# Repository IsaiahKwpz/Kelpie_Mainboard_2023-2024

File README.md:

# Kelpie_Mainboard(2023-2024)
 This is the Mainboard I designed for the kelpie robotics 2023-2024 season. It contains many sensors required to complete various tasks at the competition. It also houses an orange Pi, and a pi pico for communication across components. It is powered by a motherboard like PCB, which the mainboard is designed to slot into.

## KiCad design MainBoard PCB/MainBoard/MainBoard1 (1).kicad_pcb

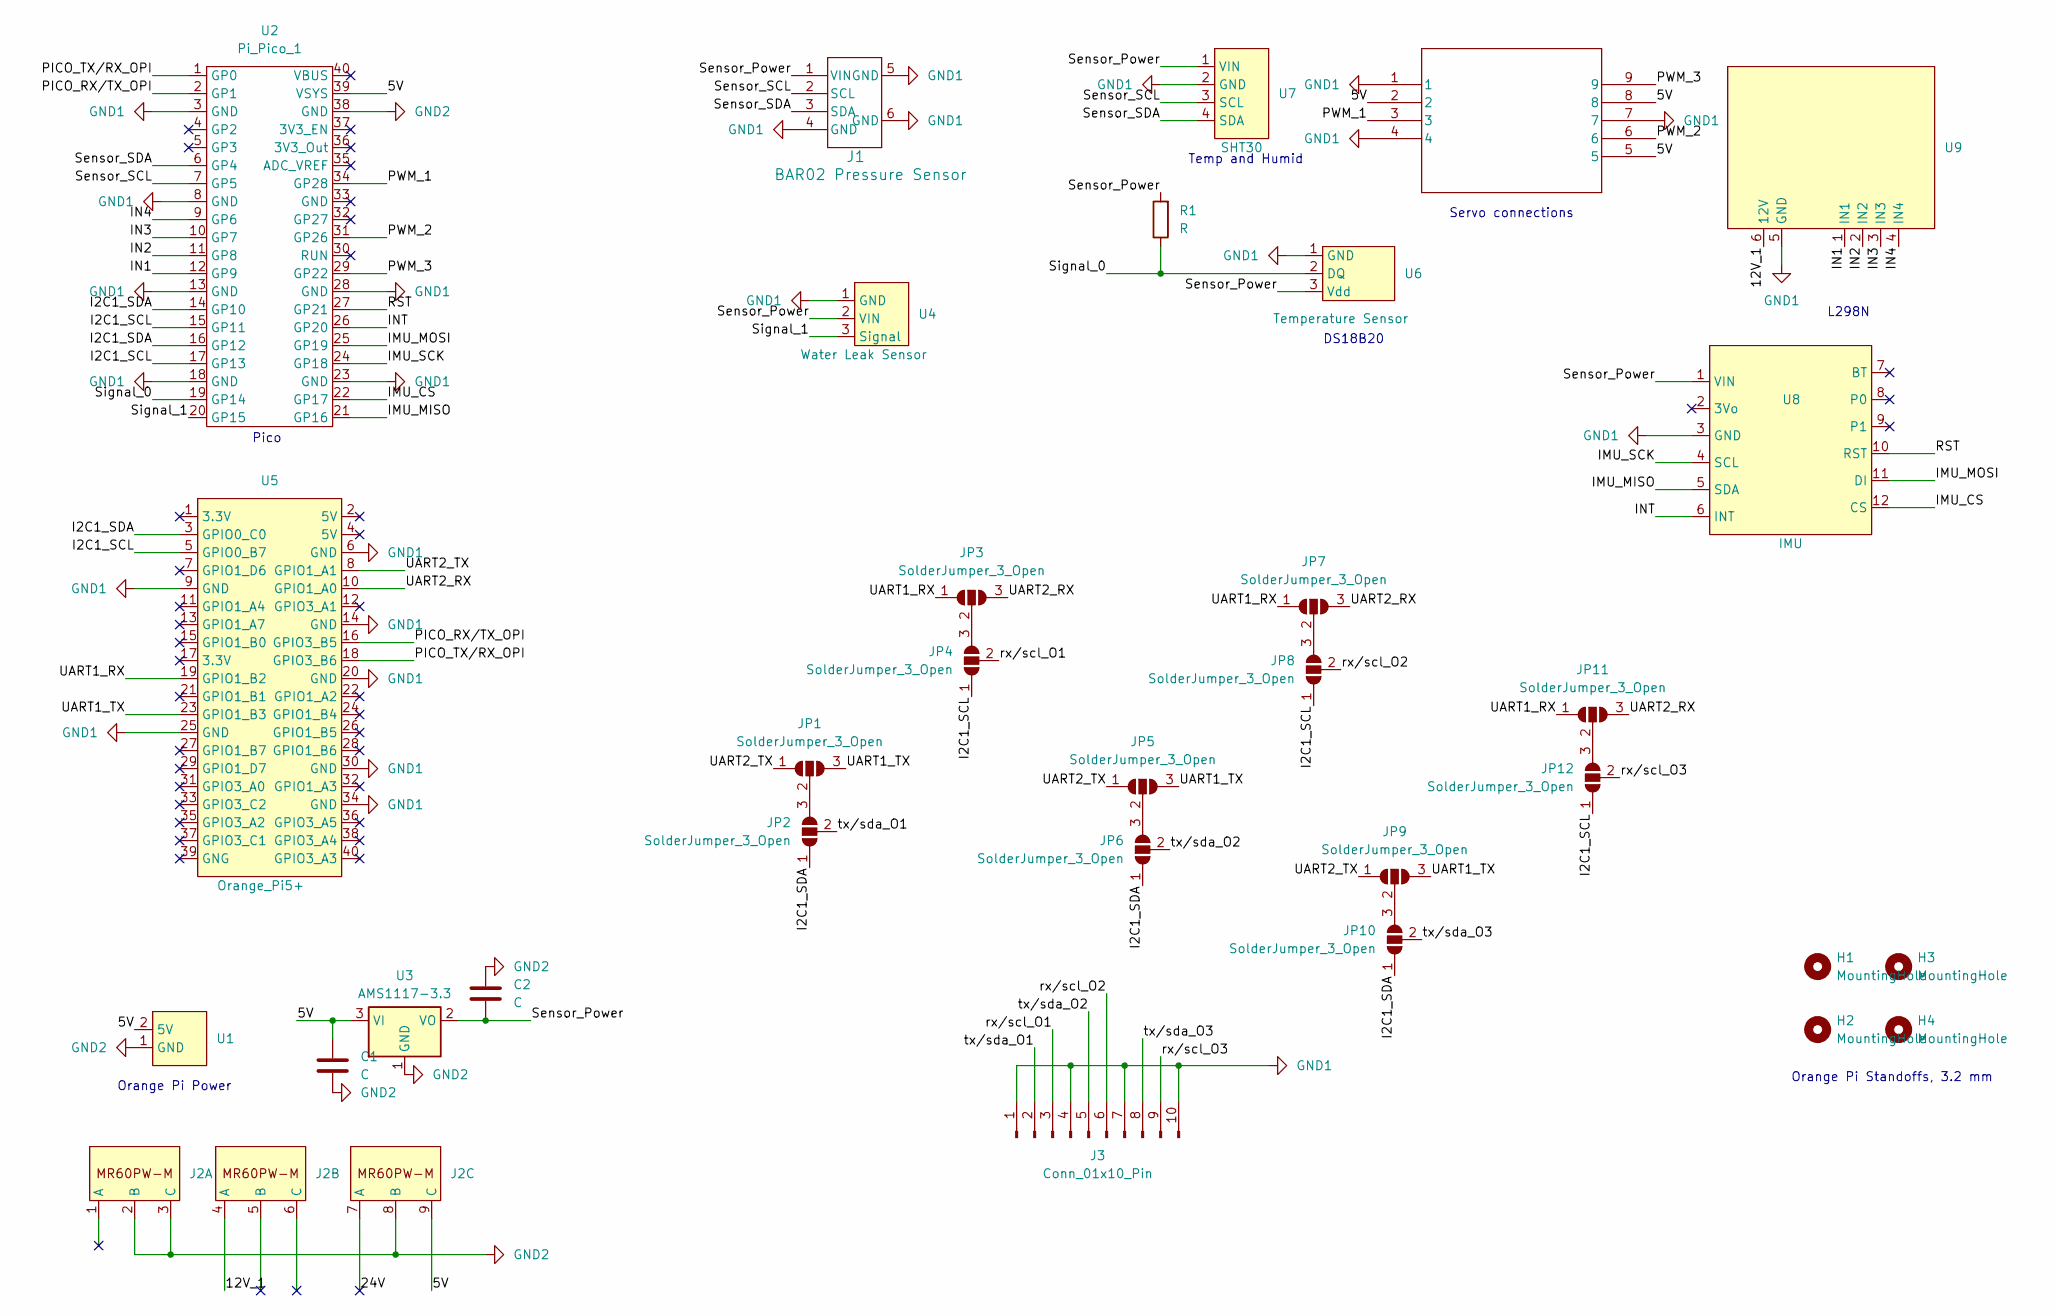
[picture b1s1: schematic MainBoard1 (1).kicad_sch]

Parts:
C1, C2: C; C_0805_2012Metric_Pad1.18x1.45mm_HandSolder
H1, H2, H3, H4: MountingHole; MountingHole_3.2mm_M3
J1: BAR02 Pressure Sensor; JST
J2: MR60PW-M_X3 (2)
J3: Conn_01x10_Pin; CardEdge_2x10 (2)
J4: TSW-103-08-G-T-RA; TSW-103-08-T-T-RA_SAI
JP1, JP2, JP3, JP4, JP5, JP6, JP7, JP8, JP9, JP10, JP11, JP12: SolderJumper_3_Open; SolderJumper-3_P2.0mm_Open_TrianglePad1.0x1.5mm
R1: R; R_0805_2012Metric_Pad1.20x1.40mm_HandSolder
U1: PinHeader_1x02_P2.54mm_Horizontal
U2: Pi_Pico_1; ESP32-S3-Pico
U3: AMS1117-3.3; SOT-223-3_TabPin2
U4: Water Leak Sensor; PinHeader_1x03_P2.54mm_Horizontal
U5: Orange_Pi5+; PinHeader_2x20_P2.54mm_Vertical
U6: Temperature Sensor; PinHeader_1x03_P2.54mm_Horizontal
U7: SHT30
U8: IMU
U9: L298N

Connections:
/5V: C1.2, J2.9 (C), J4.2, J4.5, J4.8, U1.2 (5V), U2.39 (VSYS), U3.3 (VI)
/12V_1: J2.4 (A), U9.6 (12V)
/24V: J2.7 (A)
/I2C1_SCL: JP4.1 (A), JP8.1 (A), JP12.1 (A), U2.15 (GP11), U2.17 (GP13), U5.5 (GPIO0_B7)
/I2C1_SDA: JP2.1 (A), JP6.1 (A), JP10.1 (A), U2.14 (GP10), U2.16 (GP12), U5.3 (GPIO0_C0)
/IMU_CS: U2.22 (GP17), U8.12 (CS)
/IMU_MISO: U2.21 (GP16), U8.5 (SDA)
/IMU_MOSI: U2.25 (GP19), U8.11 (DI)
/IMU_SCK: U2.24 (GP18), U8.4 (SCL)
/IN1: U2.12 (GP9), U9.1 (IN1)
/IN2: U2.11 (GP8), U9.2 (IN2)
/IN3: U2.10 (GP7), U9.3 (IN3)
/IN4: U2.9 (GP6), U9.4 (IN4)
/INT: U2.26 (GP20), U8.6 (INT)
/PICO_RX/TX_OPI: U2.2 (GP1), U5.16 (GPIO3_B5)
/PICO_TX/RX_OPI: U2.1 (GP0), U5.18 (GPIO3_B6)
/PWM_1: J4.3, U2.34 (GP28)
/PWM_2: J4.6, U2.31 (GP26)
/PWM_3: J4.9, U2.29 (GP22)
/RST: U2.27 (GP21), U8.10 (RST)
/Sensor_Power: C2.1, J1.1 (VIN), R1.2, U3.2 (VO), U4.2 (VIN), U6.3 (Vdd), U7.1 (VIN), U8.1 (VIN)
/Sensor_SCL: J1.2 (SCL), U2.7 (GP5), U7.3 (SCL)
/Sensor_SDA: J1.3 (SDA), U2.6 (GP4), U7.4 (SDA)
/Signal_0: R1.1, U2.19 (GP14), U6.2 (DQ)
/Signal_1: U2.20 (GP15), U4.3 (Signal)
/UART1_RX: JP3.1 (A), JP7.1 (A), JP11.1 (A), U5.19 (GPIO1_B2)
/UART1_TX: JP1.3 (B), JP5.3 (B), JP9.3 (B), U5.23 (GPIO1_B3)
/UART2_RX: JP3.3 (B), JP7.3 (B), JP11.3 (B), U5.10 (GPIO1_A0)
/UART2_TX: JP1.1 (A), JP5.1 (A), JP9.1 (A), U5.8 (GPIO1_A1)
/rx/scl_O1: J3.3, JP4.2 (C)
/rx/scl_O2: J3.6, JP8.2 (C)
/rx/scl_O3: J3.9, JP12.2 (C)
/tx/sda_O1: J3.2, JP2.2 (C)
/tx/sda_O2: J3.5, JP6.2 (C)
/tx/sda_O3: J3.8, JP10.2 (C)
GND1: J1.4 (GND), J1.5 (GND), J1.6 (GND), J3.1, J3.4, J3.7, J3.10, J4.1, J4.4, J4.7, U2.3 (GND), U2.8 (GND), U2.13 (GND), U2.18 (GND), U2.23 (GND), U2.28 (GND), U4.1 (GND), U5.6 (GND), U5.9 (GND), U5.14 (GND), U5.20 (GND), U5.25 (GND), U5.30 (GND), U5.34 (GND), U6.1 (GND), U7.2 (GND), U8.3 (GND), U9.5 (GND)
GND2: C1.1, C2.2, J2.2 (B), J2.3 (C), J2.8 (B), U1.1 (GND), U2.38 (GND), U3.1 (GND)
unnamed: JP1.2 (C), JP2.3 (B)
unnamed: JP3.2 (C), JP4.3 (B)
unnamed: JP5.2 (C), JP6.3 (B)
unnamed: JP7.2 (C), JP8.3 (B)
unnamed: JP9.2 (C), JP10.3 (B)
unnamed: JP11.2 (C), JP12.3 (B)

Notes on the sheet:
DS18B20
Orange Pi Power
Orange Pi Standoffs, 3.2 mm
Servo connections
Temp and Humid
L298N
Pico

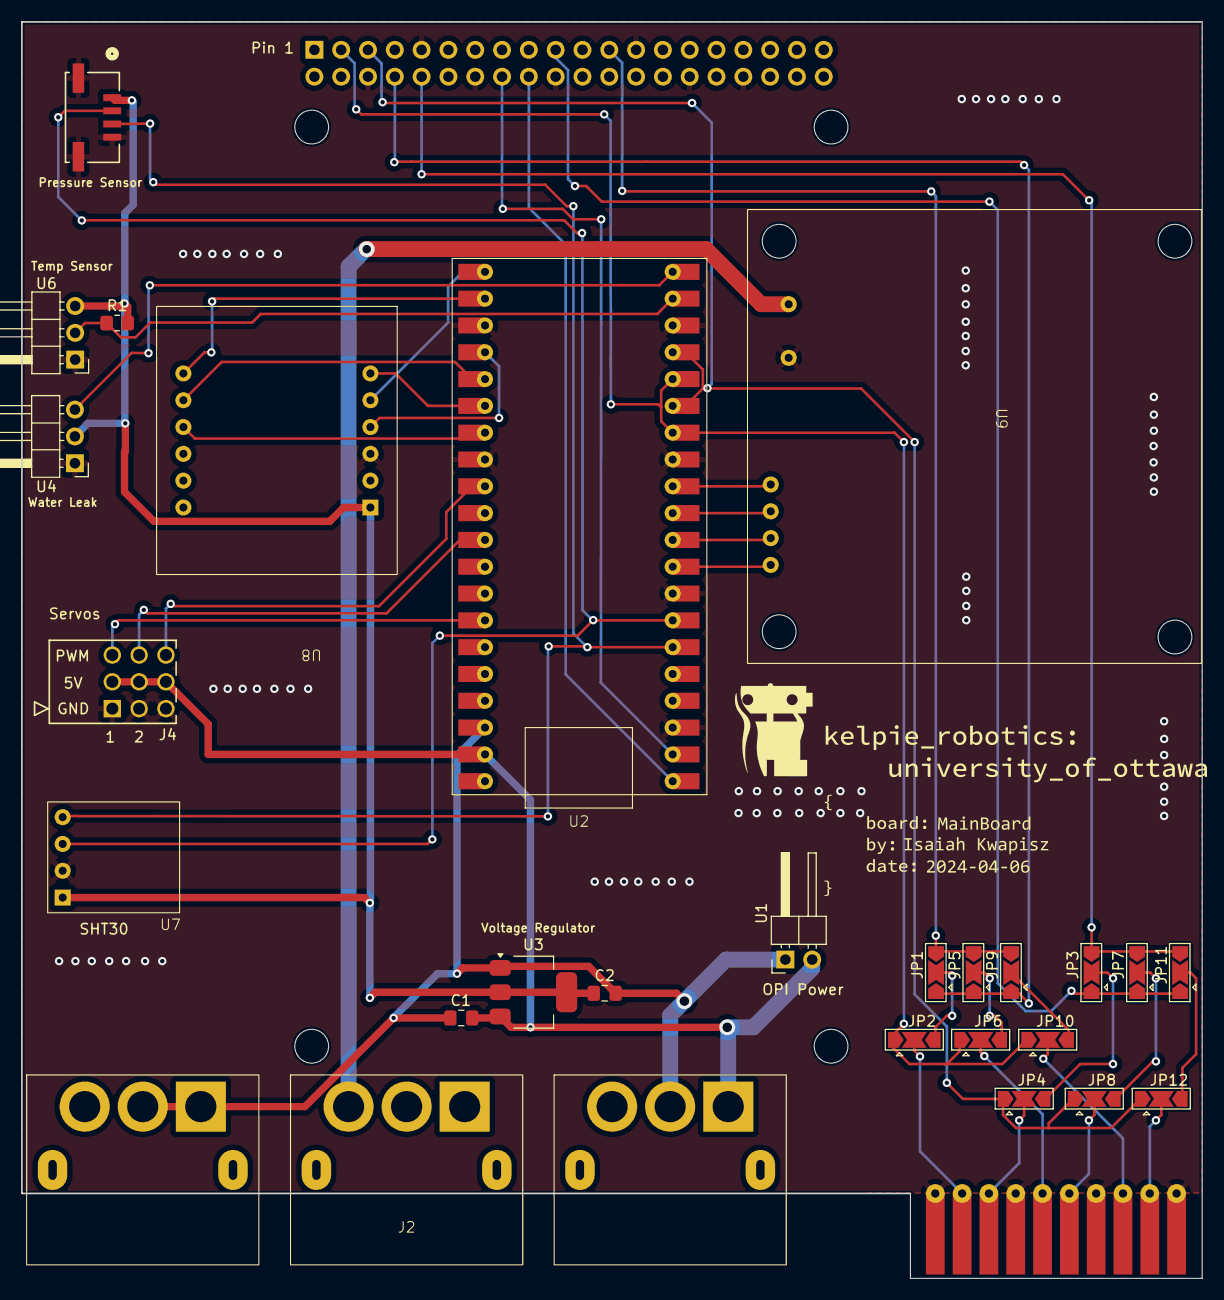
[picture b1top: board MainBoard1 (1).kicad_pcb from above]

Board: 2 copper layers, 111.8 x 119.0 mm, 32 parts (1 on the bottom side), 42 nets.

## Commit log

2024-11-26 added the files to the repo
2024-11-26 added step model and screenshots folder
2024-11-26 Added step models
2024-11-26 more step model changes
2024-11-26 Added More Screenshots
2025-01-29 added 3d cad files
2025-01-29 3d files
2025-01-29 random diffs
